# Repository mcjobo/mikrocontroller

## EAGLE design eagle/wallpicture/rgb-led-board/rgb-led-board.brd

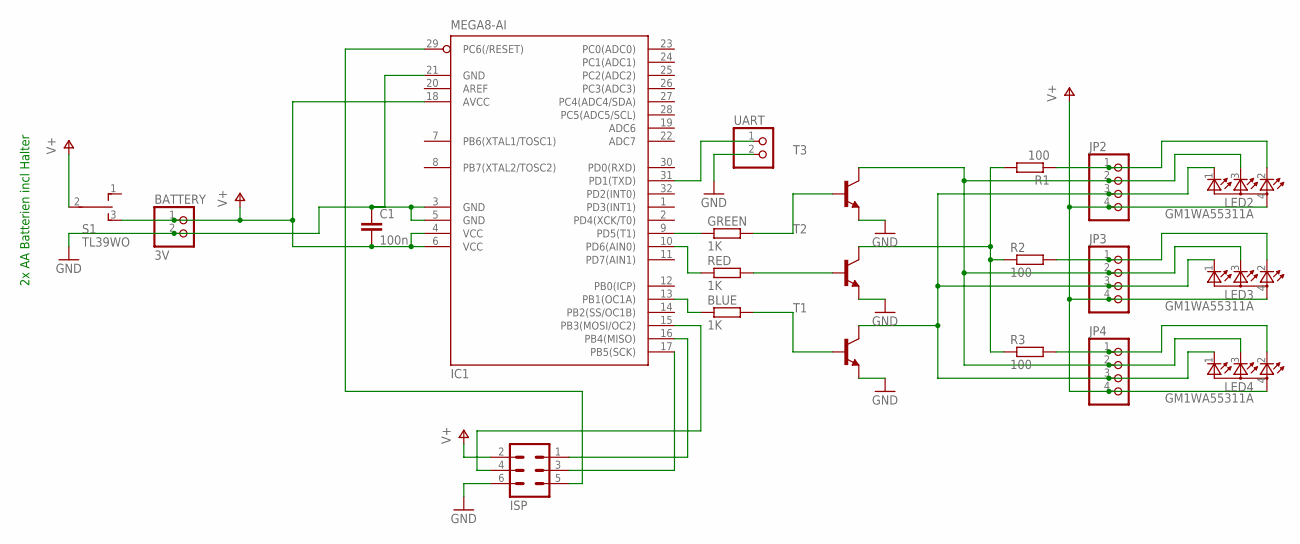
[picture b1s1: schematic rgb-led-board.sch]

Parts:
BATTERY: 3V; 1X02
BLUE: 1K; R1206
C1: 100n; C1206
GREEN: 1K; R1206
IC1: MEGA8-AI; TQFP32-08
ISP: ML6
JP2, JP3, JP4: PINHD-1X4; 1X04
LED2, LED3, LED4: GM1WA55311A
R1, R2, R3: 100; R1206
RED: 1K; R1206
S1: TL39WO; TL3XWO
T1, T2, T3: BC817-16-NPN-SOT23-BEC; SOT23-BEC
UART: PINHD-1X2; 1X02

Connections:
GND: BATTERY.2, C1.1, IC1.3 (GND), IC1.5 (GND), IC1.21 (GND), ISP.6, T1.E, T2.E, T3.E, UART.2
unnamed: GREEN.1, IC1.9 (PD5(T1))
unnamed: IC1.10 (PD6(AIN0)), RED.1
unnamed: BLUE.1, IC1.13 (PB1(OC1A))
unnamed: RED.2, T2.B
unnamed: GREEN.2, T3.B
unnamed: BLUE.2, T1.B
unnamed: JP2.1, LED2.2 (CRED), R1.1
unnamed: JP3.1, LED3.2 (CRED), R2.2
unnamed: JP4.1, LED4.2 (CRED), R3.2
unnamed: JP2.2, JP3.2, JP4.2, LED2.3 (CBLUE), LED3.3 (CBLUE), LED4.3 (CBLUE), T3.C
unnamed: R1.2, R2.1, R3.1, T2.C
unnamed: JP2.3, JP3.3, JP4.3, LED2.1 (CGREEN), LED3.1 (CGREEN), LED4.1 (CGREEN), T1.C
unnamed: IC1.31 (PD1(TXD)), UART.1
unnamed: IC1.16 (PB4(MISO)), ISP.1
unnamed: IC1.17 (PB5(SCK)), ISP.3
unnamed: IC1.29 (PC6(/RESET)), ISP.5
unnamed: IC1.15 (PB3(MOSI/OC2)), ISP.4
V+: BATTERY.1, C1.2, IC1.4 (VCC), IC1.6 (VCC), IC1.18 (AVCC), ISP.2, JP2.4, JP3.4, JP4.4, LED2.4 (A), LED3.4 (A), LED4.4 (A), S1.2, S1.3 (S)

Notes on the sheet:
2x AA Batterien incl Halter

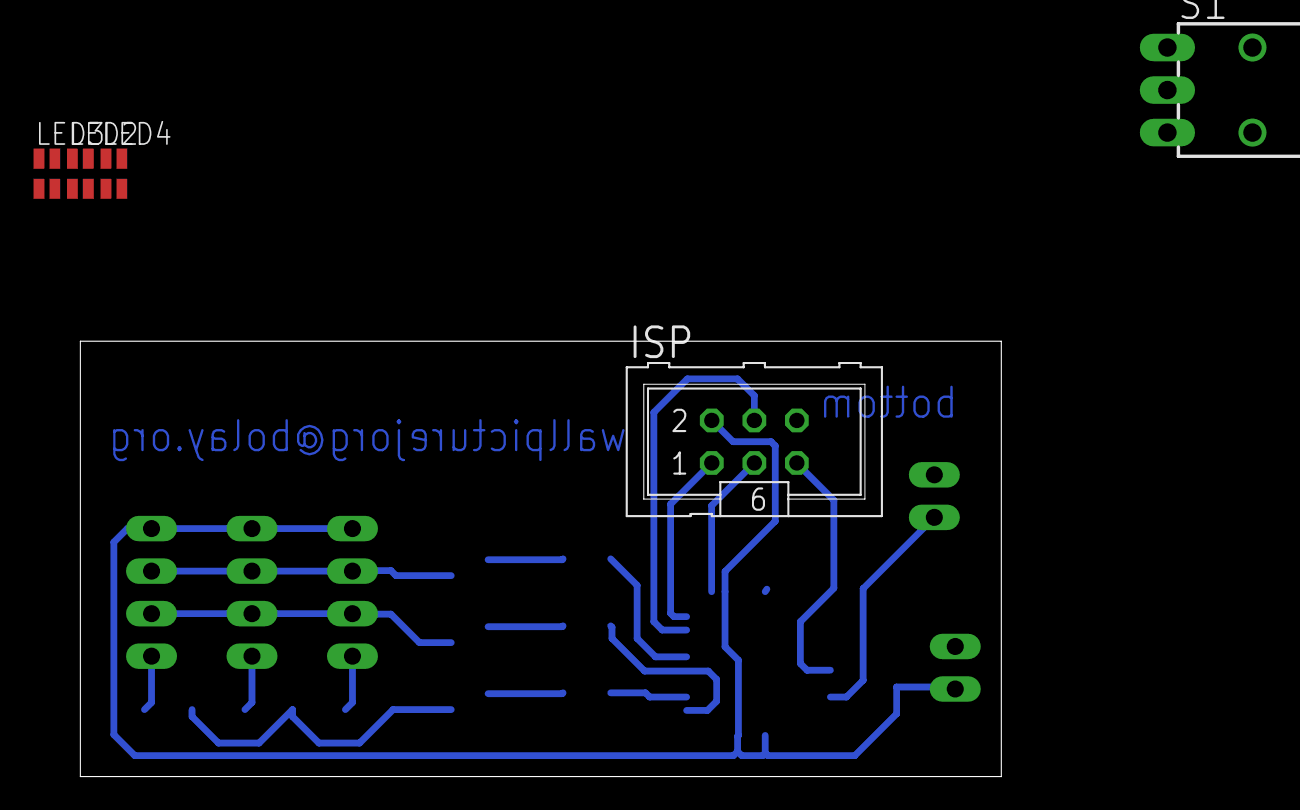
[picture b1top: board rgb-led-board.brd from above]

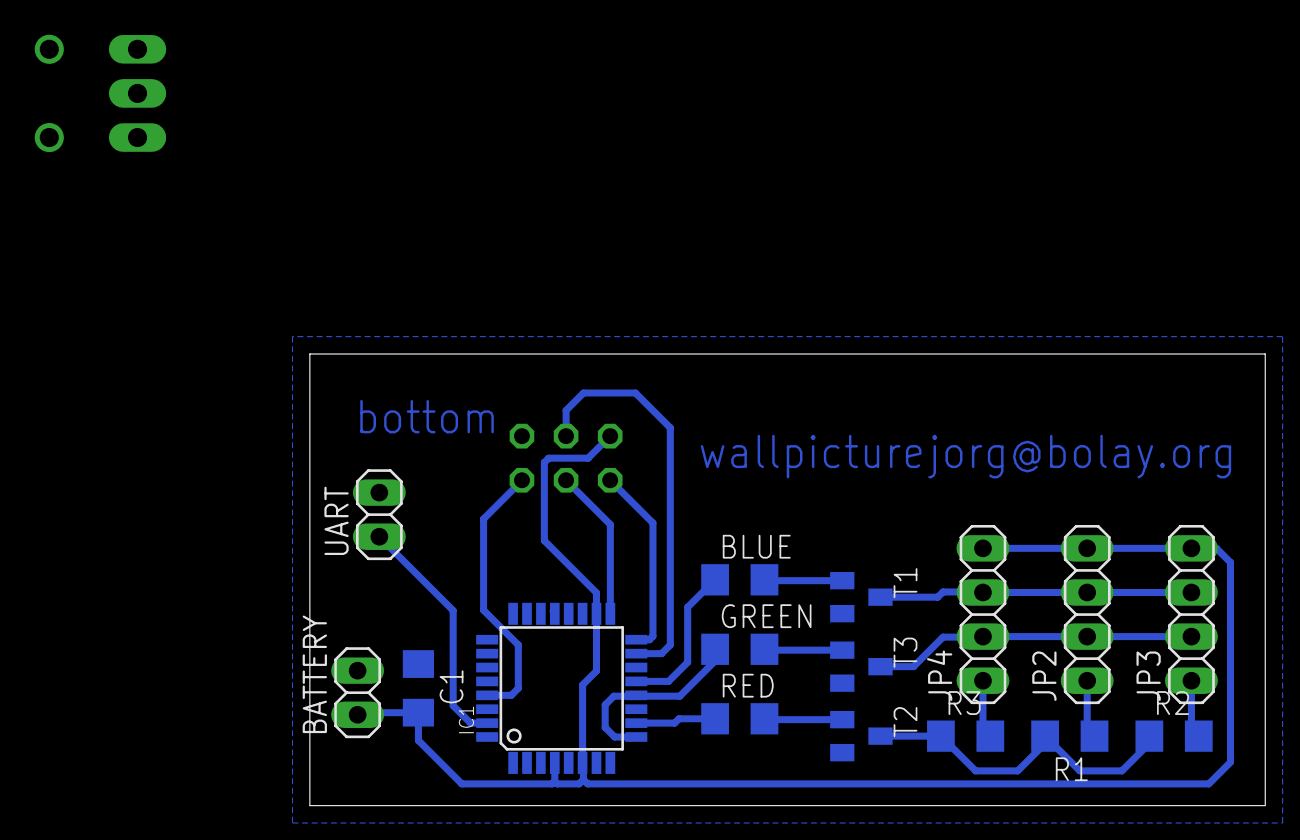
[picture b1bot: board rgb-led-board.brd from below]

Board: 2 copper layers, 55.0 x 26.0 mm, 21 parts (16 on the bottom side), 19 nets.

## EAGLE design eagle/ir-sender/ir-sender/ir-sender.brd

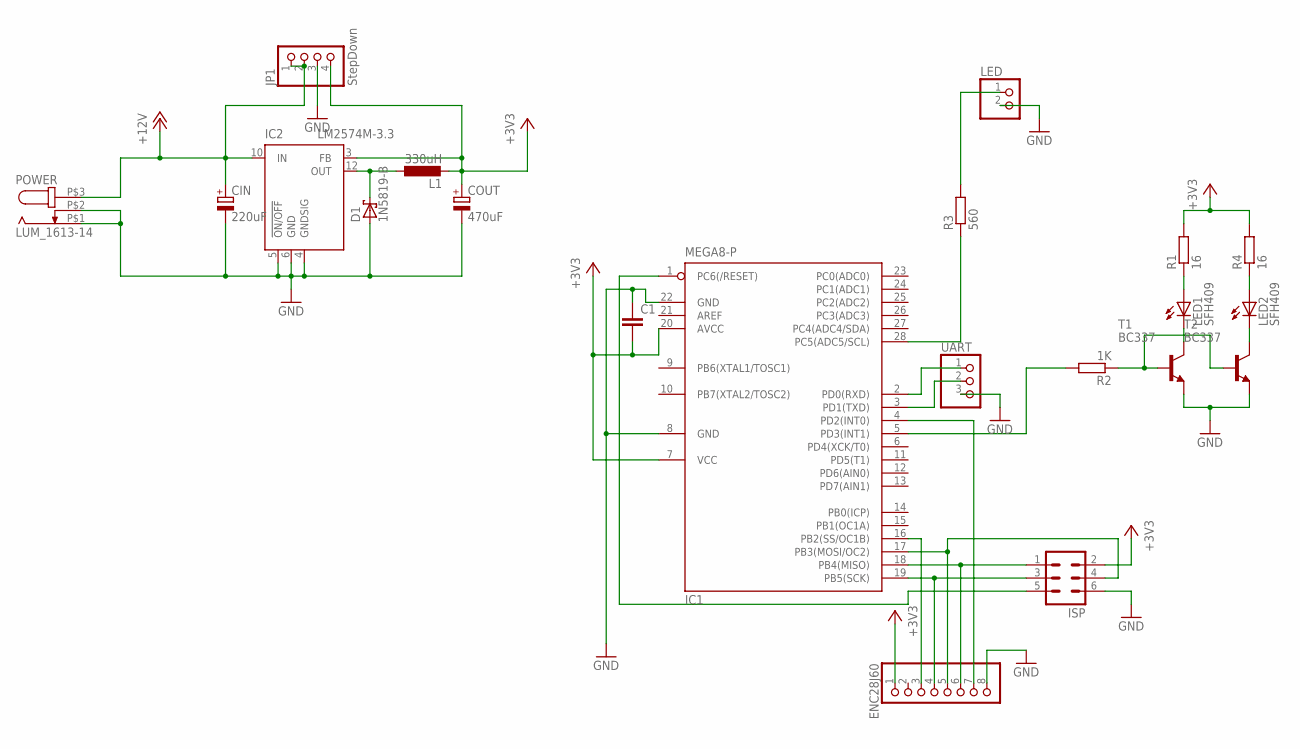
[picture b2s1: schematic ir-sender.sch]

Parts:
C1: C-EU025-030X050; C025-030X050
CIN: 220uF; E3,5-8
COUT: 470uF; E5-10,5
D1: 1N5819-B; DO41-7.6
ENC28J60: PINHD-1X8; 1X08
IC1: MEGA8-P; DIL28-3
IC2: LM2574M-3.3; SO14W
ISP: ML6
JP1: StepDown; 1X04
L1: 330uH; PIS2816
LED: PINHD-1X2; 1X02
LED1, LED2: SFH409; SFH482
POWER: LUM_1613-14; DCJ0202
R1, R4: 16; 0207/7
R2: 1K; 0207/7
R3: 560; 0207/7
T1, T2: BC337; TO92
UART: PINHD-1X3_2.54; 1X03

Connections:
+3V3: C1.2, COUT.+, ENC28J60.1, IC1.7 (VCC), IC1.20 (AVCC), IC2.3 (FB), ISP.2, JP1.4, L1.2, R1.2, R4.2
+12V: CIN.+, IC2.10 (IN), JP1.1, JP1.2, POWER.P$3 (3)
GND: C1.1, CIN.-, COUT.-, D1.A, ENC28J60.8, IC1.8 (GND), IC1.22 (GND), IC2.4 (GNDSIG), IC2.5 (!ON/OFF), IC2.6 (GND), ISP.6, JP1.3, LED.2, POWER.P$1 (1), POWER.P$2 (2), T1.1 (E), T2.1 (E), UART.3
unnamed: LED1.A, R1.1
unnamed: LED1.K (C), T1.3 (C)
unnamed: R2.1, T1.2 (B), T2.2 (B)
unnamed: D1.C, IC2.12 (OUT), L1.1
unnamed: LED.1, R3.2
unnamed: ENC28J60.4, IC1.19 (PB5(SCK)), ISP.3
unnamed: ENC28J60.5, IC1.17 (PB3(MOSI/OC2)), ISP.4
unnamed: ENC28J60.6, IC1.18 (PB4(MISO)), ISP.1
unnamed: IC1.1 (PC6(/RESET)), ISP.5
unnamed: ENC28J60.3, IC1.16 (PB2(SS/OC1B))
unnamed: IC1.28 (PC5(ADC5/SCL)), R3.1
unnamed: IC1.5 (PD3(INT1)), R2.2
unnamed: ENC28J60.7, IC1.4 (PD2(INT0))
unnamed: LED2.A, R4.1
unnamed: LED2.K (C), T2.3 (C)
unnamed: IC1.2 (PD0(RXD)), UART.1
unnamed: IC1.3 (PD1(TXD)), UART.2

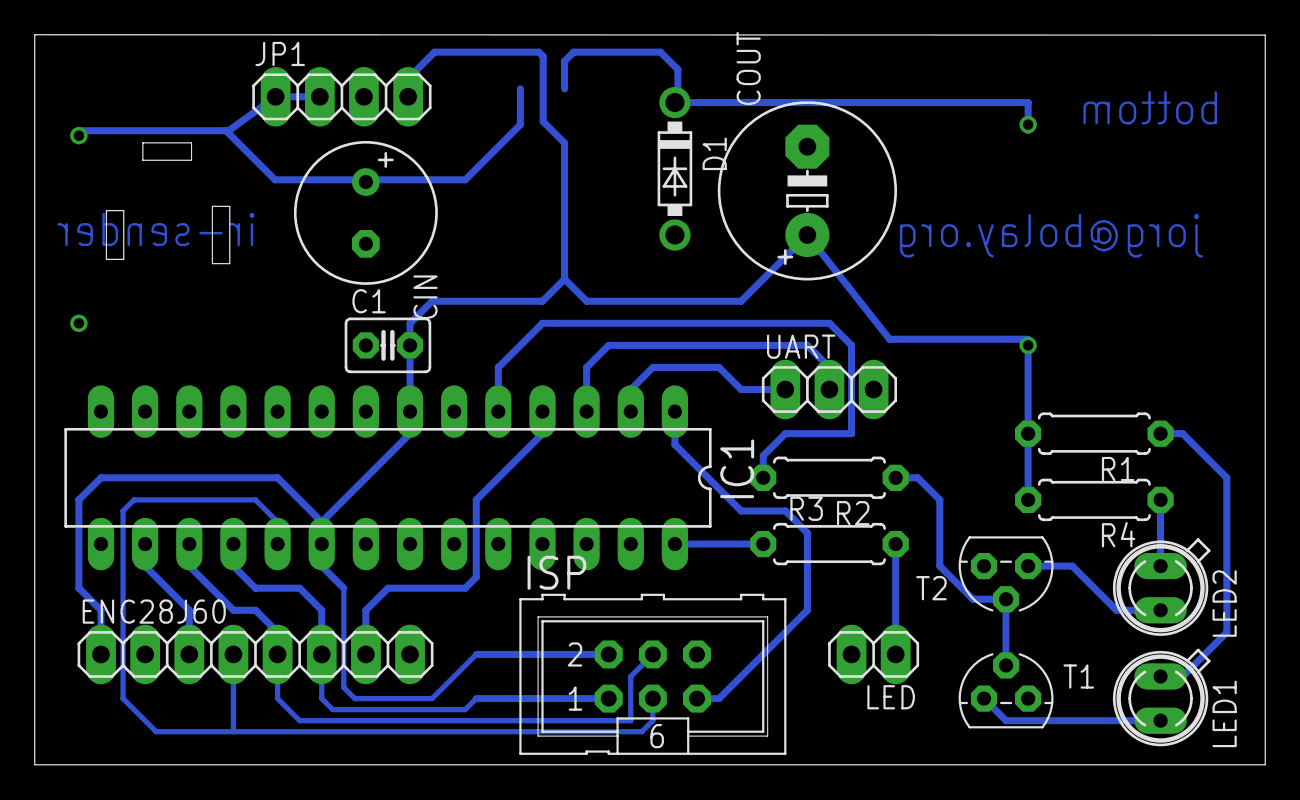
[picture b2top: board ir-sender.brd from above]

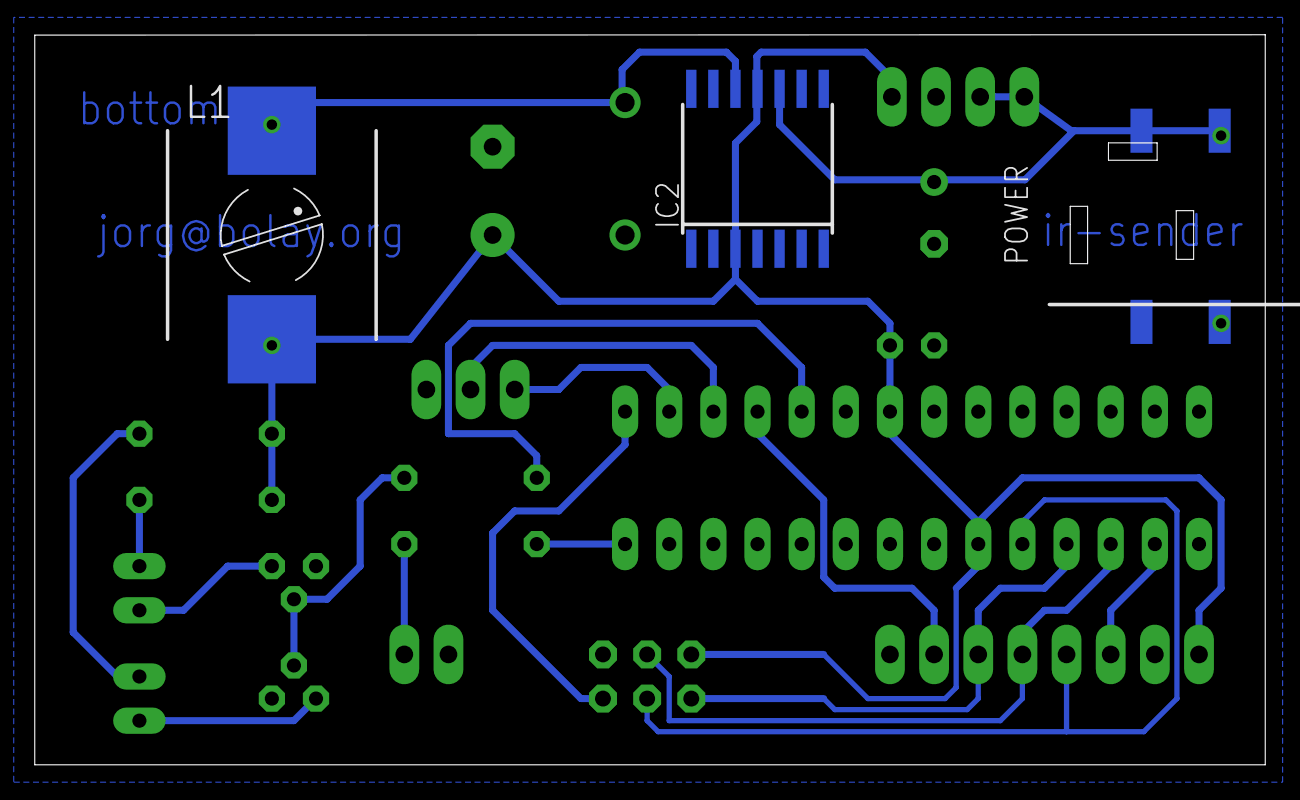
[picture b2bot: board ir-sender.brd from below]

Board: 2 copper layers, 70.8 x 42.0 mm, 22 parts (3 on the bottom side), 20 nets.

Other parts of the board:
DRILEGEND: DRILEGEND

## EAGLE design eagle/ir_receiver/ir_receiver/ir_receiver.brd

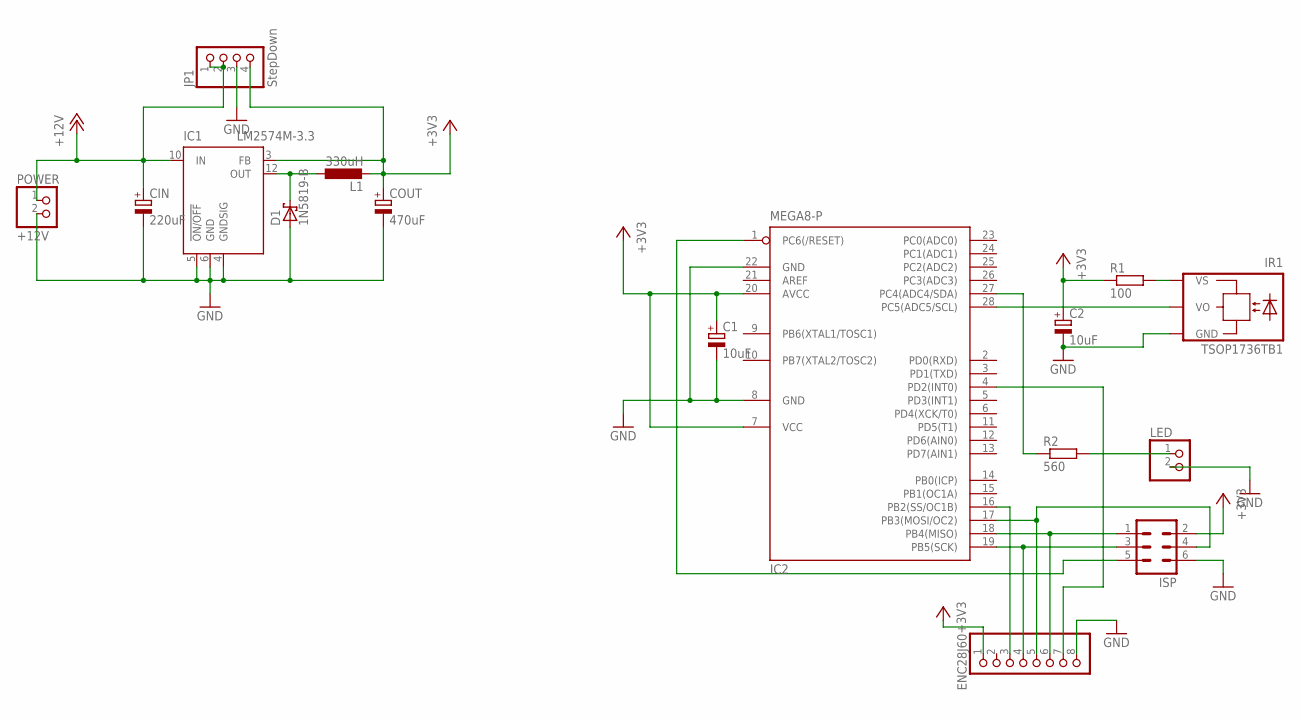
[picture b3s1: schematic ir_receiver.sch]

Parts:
C1, C2: 10uF; E2,5-5
CIN: 220uF; E3,5-8
COUT: 470uF; E5-10,5
D1: 1N5819-B; DO41-7.6
ENC28J60: PINHD-1X8; 1X08
IC1: LM2574M-3.3; SO14W
IC2: MEGA8-P; DIL28-3
IR1: TSOP1736TB1; TSOP17_TB1
ISP: ML6
JP1: StepDown; 1X04
L1: 330uH; PIS2816
LED: PINHD-1X2; 1X02
POWER: +12V; 1X02
R1: 100; 0207/7
R2: 560; 0207/7

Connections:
+3V3: C1.+, C2.+, COUT.+, ENC28J60.1, IC1.3 (FB), IC2.7 (VCC), IC2.20 (AVCC), ISP.2, JP1.4, L1.2, R1.1
+12V: CIN.+, IC1.10 (IN), JP1.1, JP1.2, POWER.1
GND: C1.-, C2.-, CIN.-, COUT.-, D1.A, ENC28J60.8, IC1.4 (GNDSIG), IC1.5 (!ON/OFF), IC1.6 (GND), IC2.8 (GND), IC2.22 (GND), IR1.GND, ISP.6, JP1.3, LED.2, POWER.2
unnamed: IC2.27 (PC4(ADC4/SDA)), R2.1
unnamed: IC2.28 (PC5(ADC5/SCL)), IR1.VO
unnamed: D1.C, IC1.12 (OUT), L1.1
unnamed: LED.1, R2.2
unnamed: IR1.VS, R1.2
unnamed: ENC28J60.4, IC2.19 (PB5(SCK)), ISP.3
unnamed: ENC28J60.5, IC2.17 (PB3(MOSI/OC2)), ISP.4
unnamed: ENC28J60.6, IC2.18 (PB4(MISO)), ISP.1
unnamed: IC2.1 (PC6(/RESET)), ISP.5
unnamed: ENC28J60.3, IC2.16 (PB2(SS/OC1B))
unnamed: ENC28J60.7, IC2.4 (PD2(INT0))

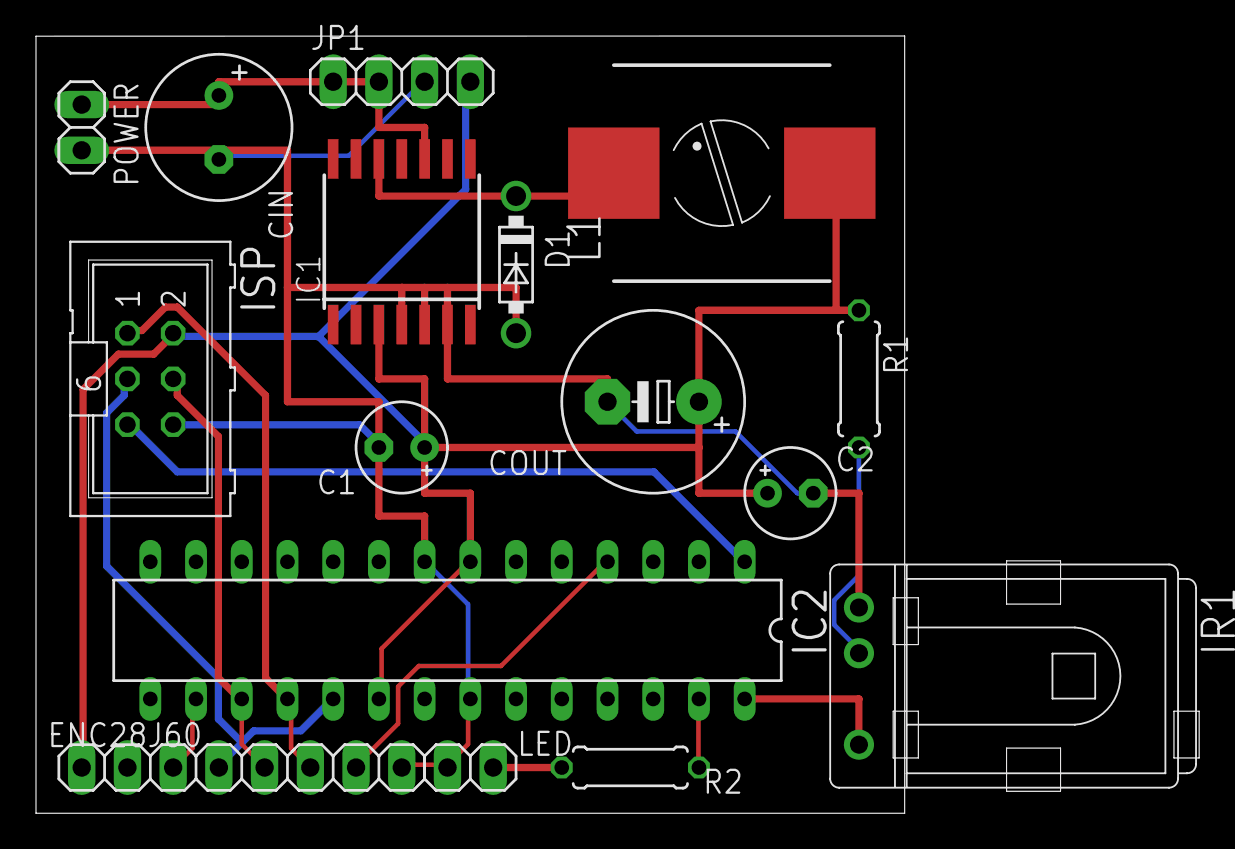
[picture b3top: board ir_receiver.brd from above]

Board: 2 copper layers, 48.3 x 43.2 mm, 16 parts (0 on the bottom side), 14 nets.

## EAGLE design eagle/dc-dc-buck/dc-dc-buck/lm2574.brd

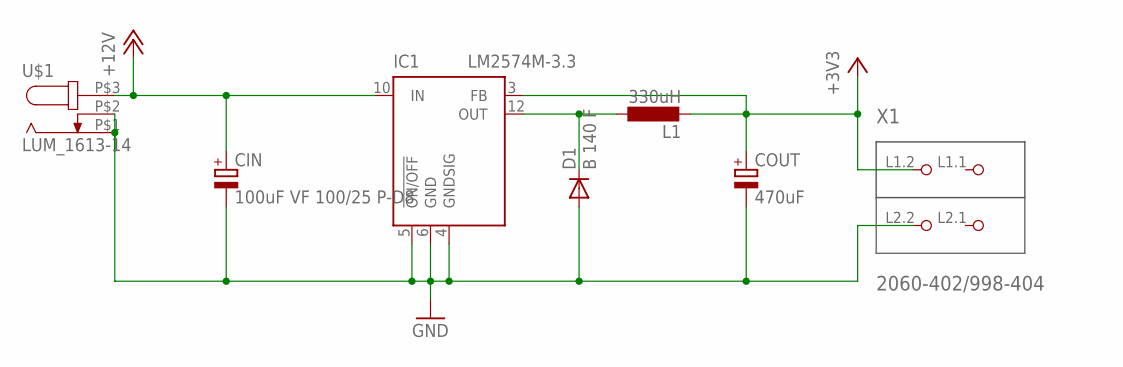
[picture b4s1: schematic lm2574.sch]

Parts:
CIN: 100uF VF 100/25 P-D8; 153CLV-0605
COUT: 470uF; 153CLV-0810
D1: B 140 F; DO-214AC
IC1: LM2574M-3.3; SO14W
L1: 330uH; PIS2816
U$1: LUM_1613-14; DCJ0202
X1: 2060-402/998-404; P-2060-402/998-404

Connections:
+3V3: COUT.+, IC1.3 (FB), L1.2, X1.L1.2 (P1.2)
+12V: CIN.+, IC1.10 (IN), U$1.P$3 (3)
GND: CIN.-, COUT.-, D1.A, IC1.4 (GNDSIG), IC1.5 (!ON/OFF), IC1.6 (GND), U$1.P$1 (1), U$1.P$2 (2), X1.L2.2 (P2.2)
unnamed: D1.C, IC1.12 (OUT), L1.1

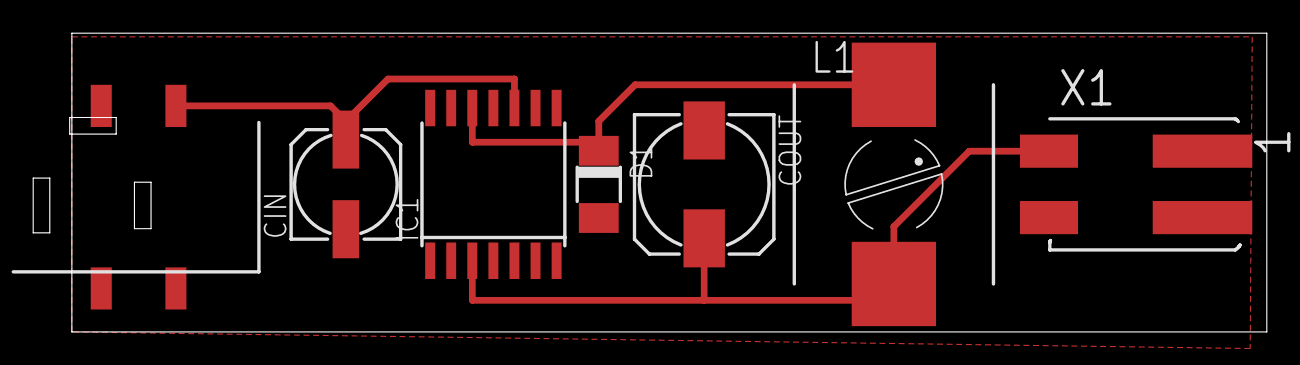
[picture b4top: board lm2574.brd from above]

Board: 2 copper layers, 74.3 x 18.0 mm, 7 parts (0 on the bottom side), 4 nets.

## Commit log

2013-09-02 commited test
2013-09-07 added rfm12 testboard project
2013-09-16 removed the packet type or address field because it needs to be in the higher layer
2013-09-16 fixed something don't realy know what's going on
2013-09-16 added solution file
2013-09-23 added protocol implementation
2013-09-27 added statemachine files
2013-09-27 added timer functions
2013-09-27 changed symbols from atmega8 to atmega 88A
2013-10-06 ÜbungsProjekt TestBoard
2013-10-12 added rfm12 module and fixed project setup to create library
2013-10-12 fixing problems with ack creation of protocol
2013-10-12 added procyon avrlib to the project
2013-10-12 build rfm12 as library and have the protocol implementation also as library
2013-10-16 fixed the rfm12 library to work again as a static library
2013-10-17 added network components
2013-10-19 added openmcp project
2013-10-29 reimplemented the protocol impl to have a proper state maschine and clean code
2013-10-29 moved new protocol in place
2013-10-31 reducing size of project
2013-10-31 first try in connecting io-board to openhab
2013-11-03 added basic sending capabilities to openhab port impl
2013-12-26 reimplemented statemachine to rfm12 library to working state
2013-12-31 added additional lib to project
2013-12-31 new project to build a driver for led strips with PWM LDR and motion sensor
2014-01-02 uart project from peter leury
2014-02-01 breadboard type of prototypeworking + added a2d lib
2015-11-03 initial commit ir-receiver + sender
2015-11-08 ir_receive project
2015-11-08 ir_send vorläufig fertig
2015-11-08 common files
2015-12-11 projekt weinachtsbild beleuchtung working
2015-12-11 changed uart lib to use the smarthomatic one and use a extra lib for leds
2015-12-11 just a simple project to test the uart connection
2015-12-11 sublime project files
2015-12-11 changed to other uart lib
2015-12-11 don't know where i am just saving
2015-12-11 added eagle files to repo
2015-12-11 added kicad files to the repo
2015-12-12 fixed 12V on motion sensor and other components
2015-12-12 fiddleling with MAC adresses
2015-12-14 added component lines + enclosure infos
2016-01-02 added custom footprints and finished schematic
2016-01-02 changed string parsing to hex numbers added ir protocols for micha
2016-01-09 changed ir_receiver output to hex
2016-02-15 motion sensor project in kicad
2016-11-05 motion sensor Projekt für Küche und unter dem Bett
2016-11-05 initiales Projekt Switchboard
2016-11-05 motion sensor projekt
2016-11-05 bibliotheks aenderungen
2016-11-05 programm für das Bewegungsmelder Projekt
2016-11-06 der switchboard schaltplan wurde angefangen
2016-12-20 added switchboard project
2016-12-21 changed files of motion sensor project and library
2016-12-25 zusätzliche modi beim motion sensor: 0: off 1: on 2: bewegung
2016-12-26 fading funktioniert beschreibungsdatei für mqtt topics hinzugefügt mqtt topics im ino file etwas auseinandergezogen
2016-12-26 rduino projekt
